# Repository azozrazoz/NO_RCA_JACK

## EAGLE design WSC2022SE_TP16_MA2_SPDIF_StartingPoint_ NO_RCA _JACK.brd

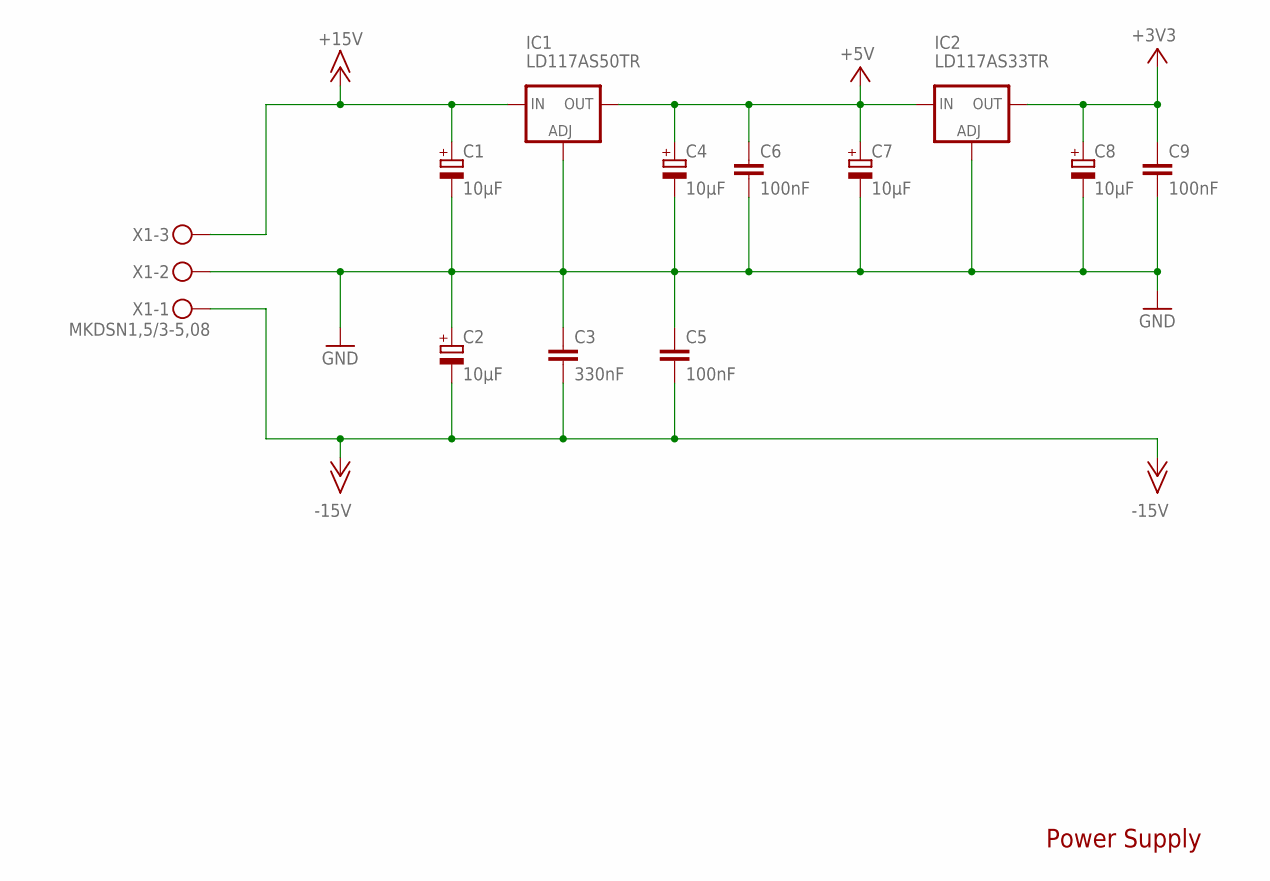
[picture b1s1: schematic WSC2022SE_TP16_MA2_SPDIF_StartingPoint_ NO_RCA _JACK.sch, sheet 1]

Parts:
C1, C2, C4, C7, C8: 10µF; CT3528
C3: 330nF; C0805
C5, C6, C9: 100nF; C0805
IC1: LD117AS50TR; SOT223
IC2: LD117AS33TR; SOT223
X1: MKDSN1,5/3-5,08

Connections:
+3V3: C8.+, C9.1, IC2.2 (OUT), IC2.4 (OUT); also elsewhere on the board
+5V: C4.+, C6.1, C7.+, IC1.2 (OUT), IC1.4 (OUT), IC2.3 (IN); also elsewhere on the board
+15V: C1.+, IC1.3 (IN), X1.3; also elsewhere on the board
-15V: C2.-, C3.2, C5.2, X1.1; also elsewhere on the board
GND: C1.-, C2.+, C3.1, C4.-, C5.1, C6.2, C7.-, C8.-, C9.2, IC1.1 (ADJ), IC2.1 (ADJ), X1.2; also elsewhere on the board

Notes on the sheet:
Power Supply

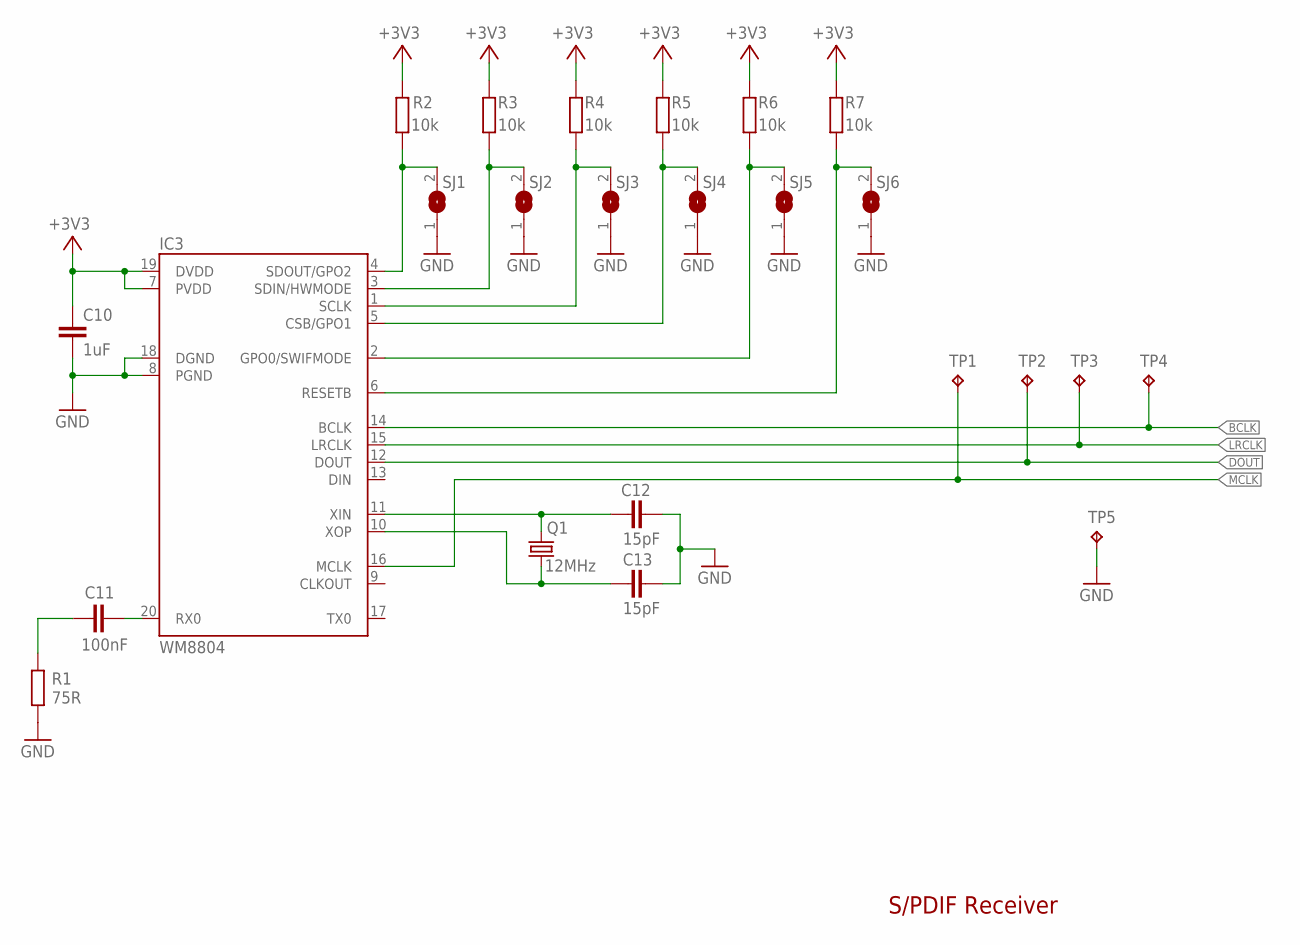
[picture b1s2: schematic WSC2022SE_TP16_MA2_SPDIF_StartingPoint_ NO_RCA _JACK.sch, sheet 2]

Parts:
C10: 1uF; C0805
C11: 100nF; C0805
C12, C13: 15pF; C0805
IC3: WM8804; SSOP20BU
Q1: 12MHz; 5.0X3.2_2
R1: 75R; R0805
R2, R3, R4, R5, R6, R7: 10k; R0805
SJ1, SJ2, SJ3, SJ4, SJ5, SJ6: SJ
TP1, TP2, TP3, TP4, TP5: TPB2,54; B2,54

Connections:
+3V3: C10.1, IC3.7 (PVDD), IC3.19 (DVDD), R2.2, R3.2, R4.2, R5.2, R6.2, R7.2; also elsewhere on the board
BCLK: IC3.14 (BCLK), TP4.TP; also elsewhere on the board
DOUT: IC3.12 (DOUT), TP2.TP; also elsewhere on the board
GND: C10.2, C12.1, C13.1, IC3.8 (PGND), IC3.18 (DGND), R1.1, SJ1.1, SJ2.1, SJ3.1, SJ4.1, SJ5.1, SJ6.1, TP5.TP; also elsewhere on the board
LRCLK: IC3.15 (LRCLK), TP3.TP; also elsewhere on the board
MCLK: IC3.16 (MCLK), TP1.TP; also elsewhere on the board
unnamed: C11.1, R1.2
unnamed: C11.2, IC3.20 (RX0)
unnamed: C13.2, IC3.10 (XOP), Q1.1
unnamed: C12.2, IC3.11 (XIN), Q1.2
unnamed: IC3.4 (SDOUT/GPO2), R2.1, SJ1.2
unnamed: IC3.1 (SCLK), R4.1, SJ3.2
unnamed: IC3.2 (GPO0/SWIFMODE), R6.1, SJ5.2
unnamed: IC3.6 (RESETB), R7.1, SJ6.2
unnamed: IC3.5 (CSB/GPO1), R5.1, SJ4.2
unnamed: IC3.3 (SDIN/HWMODE), R3.1, SJ2.2

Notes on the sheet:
S/PDIF Receiver

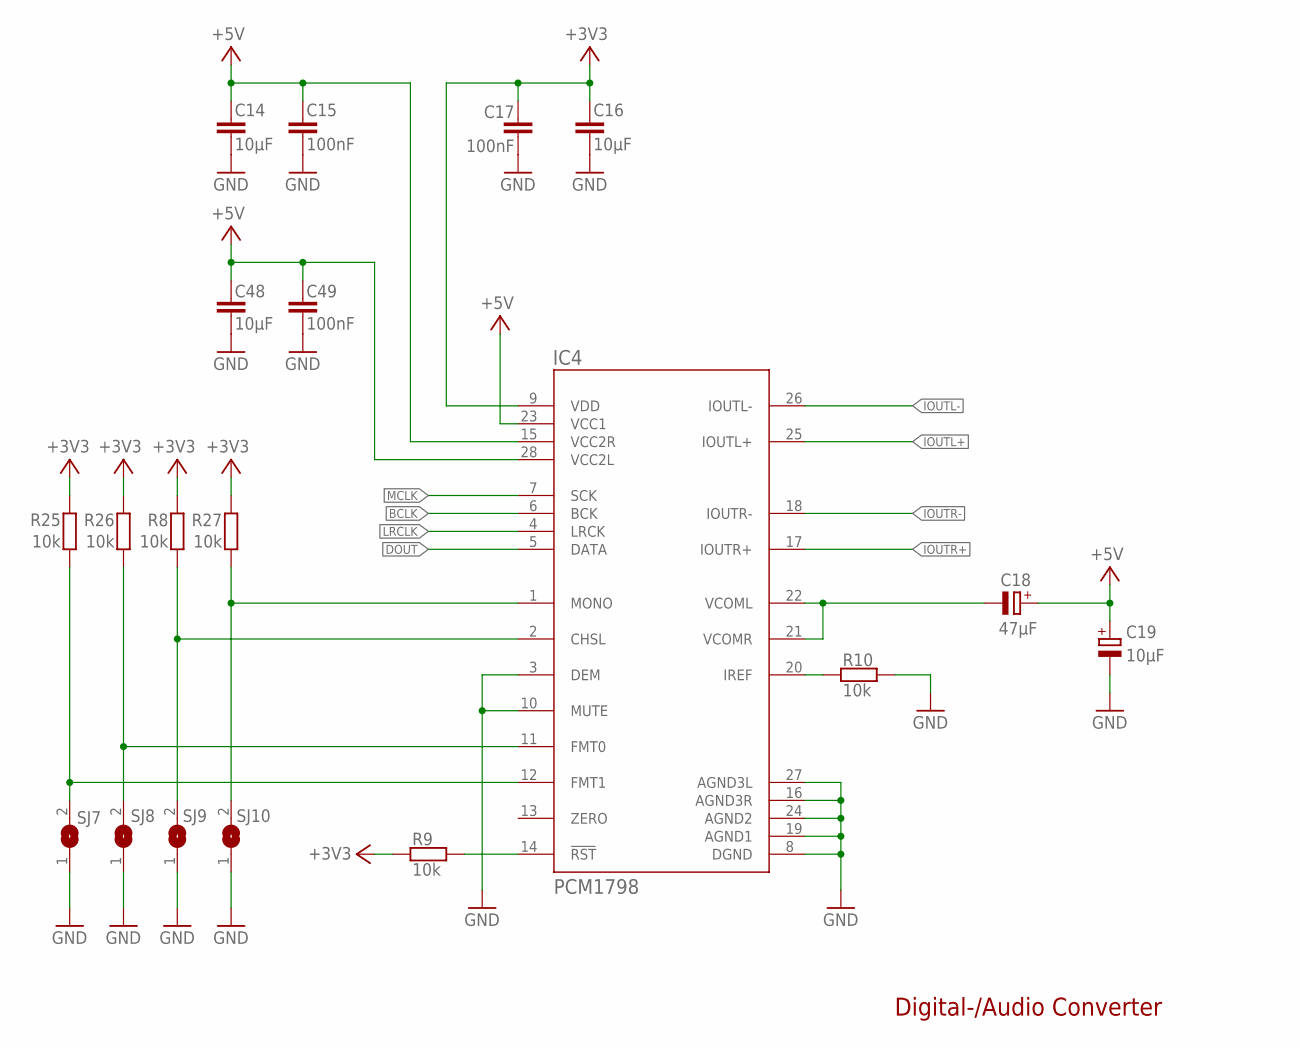
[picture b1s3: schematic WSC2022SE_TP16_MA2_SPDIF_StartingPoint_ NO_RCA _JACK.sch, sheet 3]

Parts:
C14, C16, C48: 10µF; C0805
C15, C17, C49: 100nF; C0805
C18: 47µF; PANASONIC_C
C19: 10µF; PANASONIC_B
IC4: PCM1798; SSOP28
R8, R9, R10, R25, R26, R27: 10k; R0805
SJ7, SJ8, SJ9, SJ10: SJ

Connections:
+3V3: C16.2, C17.2, IC4.9 (VDD), R8.1, R9.1, R25.1, R26.1, R27.1; also elsewhere on the board
+5V: C14.1, C15.1, C18.+, C19.+, C48.1, C49.1, IC4.15 (VCC2R), IC4.23 (VCC1), IC4.28 (VCC2L); also elsewhere on the board
BCLK: IC4.6 (BCK); also elsewhere on the board
DOUT: IC4.5 (DATA); also elsewhere on the board
GND: C14.2, C15.2, C16.1, C17.1, C19.-, C48.2, C49.2, IC4.3 (DEM), IC4.8 (DGND), IC4.10 (MUTE), IC4.16 (AGND3R), IC4.19 (AGND1), IC4.24 (AGND2), IC4.27 (AGND3L), R10.2, SJ7.1, SJ8.1, SJ9.1, SJ10.1; also elsewhere on the board
IOUTL+: IC4.25 (IOUTL+); also elsewhere on the board
IOUTL-: IC4.26 (IOUTL-); also elsewhere on the board
IOUTR+: IC4.17 (IOUTR+); also elsewhere on the board
IOUTR-: IC4.18 (IOUTR-); also elsewhere on the board
LRCLK: IC4.4 (LRCK); also elsewhere on the board
MCLK: IC4.7 (SCK); also elsewhere on the board
unnamed: IC4.1 (MONO), R27.2, SJ10.2
unnamed: IC4.14 (!RST), R9.2
unnamed: IC4.20 (IREF), R10.1
unnamed: C18.-, IC4.21 (VCOMR), IC4.22 (VCOML)
unnamed: IC4.11 (FMT0), R26.2, SJ8.2
unnamed: IC4.12 (FMT1), R25.2, SJ7.2
unnamed: IC4.2 (CHSL), R8.2, SJ9.2

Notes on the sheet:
Digital-/Audio Converter

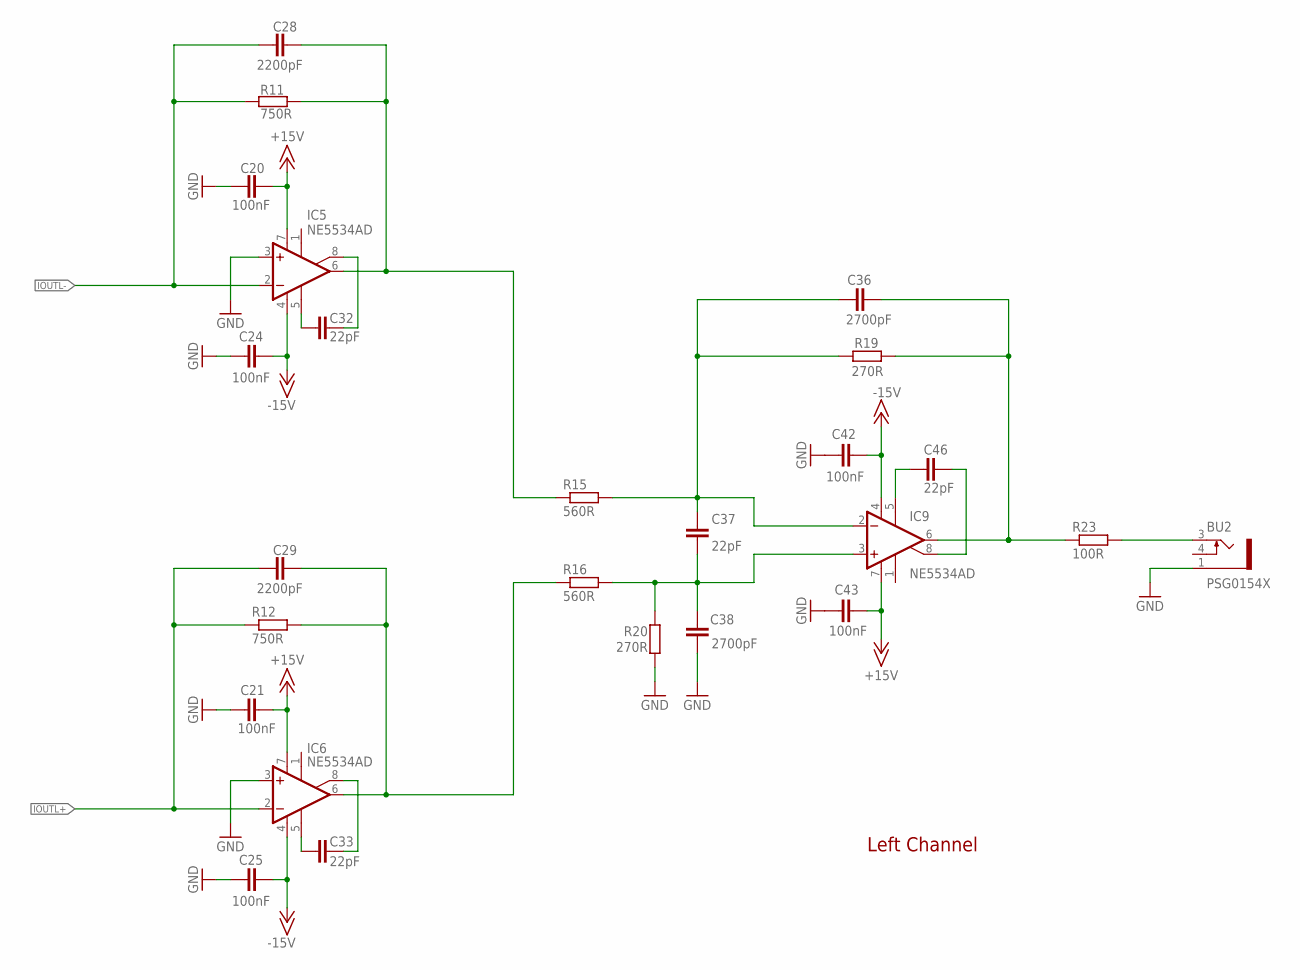
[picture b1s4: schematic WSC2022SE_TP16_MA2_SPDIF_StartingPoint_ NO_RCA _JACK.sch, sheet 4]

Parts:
BU2: PSG0154X; PHONO-3P
C20, C21, C24, C25, C42, C43: 100nF; C0805
C28, C29: 2200pF; C0805
C32, C33, C37, C46: 22pF; C0805
C36, C38: 2700pF; C0805
IC5, IC6, IC9: NE5534AD; SO08
R11, R12: 750R; R0805
R15, R16: 560R; R0805
R19, R20: 270R; R0805
R23: 100R; R0805

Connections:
+15V: C20.1, C21.1, C43.1, IC5.7 (V+), IC6.7 (V+), IC9.7 (V+); also elsewhere on the board
-15V: C24.1, C25.1, C42.1, IC5.4 (V-), IC6.4 (V-), IC9.4 (V-); also elsewhere on the board
GND: BU2.1, C20.2, C21.2, C24.2, C25.2, C38.2, C42.2, C43.2, IC5.3 (+IN), IC6.3 (+IN), R20.1; also elsewhere on the board
IOUTL+: C29.1, IC6.2 (-IN), R12.1; also elsewhere on the board
IOUTL-: C28.1, IC5.2 (-IN), R11.1; also elsewhere on the board
unnamed: C33.1, IC6.8 (ON/CMP)
unnamed: C33.2, IC6.5 (CMP)
unnamed: C37.2, C38.1, IC9.3 (+IN), R16.2, R20.2
unnamed: C32.2, IC5.5 (CMP)
unnamed: C32.1, IC5.8 (ON/CMP)
unnamed: C36.2, C37.1, IC9.2 (-IN), R15.2, R19.1
unnamed: C36.1, IC9.6 (OUT), R19.2, R23.1
unnamed: C46.1, IC9.5 (CMP)
unnamed: C46.2, IC9.8 (ON/CMP)
OUT-CHANNEL-L: BU2.3, R23.2
VOUTL+: C29.2, IC6.6 (OUT), R12.2, R16.1
VOUTL-: C28.2, IC5.6 (OUT), R11.2, R15.1

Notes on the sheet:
Left Channel

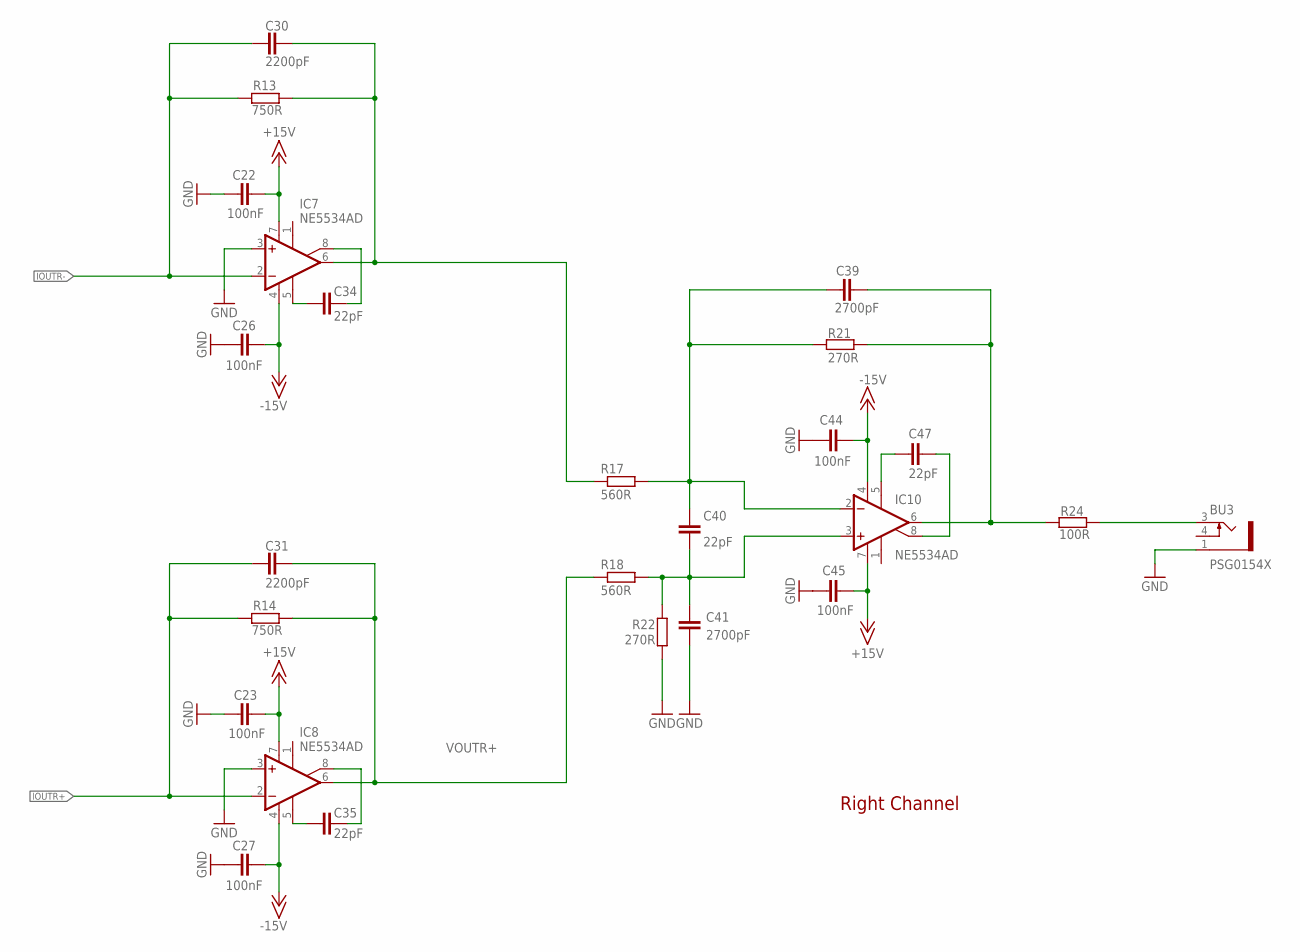
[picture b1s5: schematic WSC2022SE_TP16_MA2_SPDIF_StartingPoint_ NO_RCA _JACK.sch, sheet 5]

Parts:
BU3: PSG0154X; PHONO-3P
C22, C23, C26, C27, C44, C45: 100nF; C0805
C30, C31: 2200pF; C0805
C34, C35, C40, C47: 22pF; C0805
C39, C41: 2700pF; C0805
IC7, IC8, IC10: NE5534AD; SO08
R13, R14: 750R; R0805
R17, R18: 560R; R0805
R21, R22: 270R; R0805
R24: 100R; R0805

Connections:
+15V: C22.1, C23.1, C45.1, IC7.7 (V+), IC8.7 (V+), IC10.7 (V+); also elsewhere on the board
-15V: C26.1, C27.1, C44.1, IC7.4 (V-), IC8.4 (V-), IC10.4 (V-); also elsewhere on the board
GND: BU3.1, C22.2, C23.2, C26.2, C27.2, C41.2, C44.2, C45.2, IC7.3 (+IN), IC8.3 (+IN), R22.1; also elsewhere on the board
IOUTR+: C31.1, IC8.2 (-IN), R14.1; also elsewhere on the board
IOUTR-: C30.1, IC7.2 (-IN), R13.1; also elsewhere on the board
unnamed: C34.1, IC7.8 (ON/CMP)
unnamed: C39.2, C40.1, IC10.2 (-IN), R17.2, R21.1
unnamed: C39.1, IC10.6 (OUT), R21.2, R24.1
unnamed: C47.1, IC10.5 (CMP)
unnamed: C47.2, IC10.8 (ON/CMP)
unnamed: C34.2, IC7.5 (CMP)
unnamed: C40.2, C41.1, IC10.3 (+IN), R18.2, R22.2
unnamed: C35.1, IC8.8 (ON/CMP)
unnamed: C35.2, IC8.5 (CMP)
OUT-CHANNEL-R: BU3.3, R24.2
VOUTR+: C31.2, IC8.6 (OUT), R14.2, R18.1
VOUTR-: C30.2, IC7.6 (OUT), R13.2, R17.1

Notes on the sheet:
Right Channel

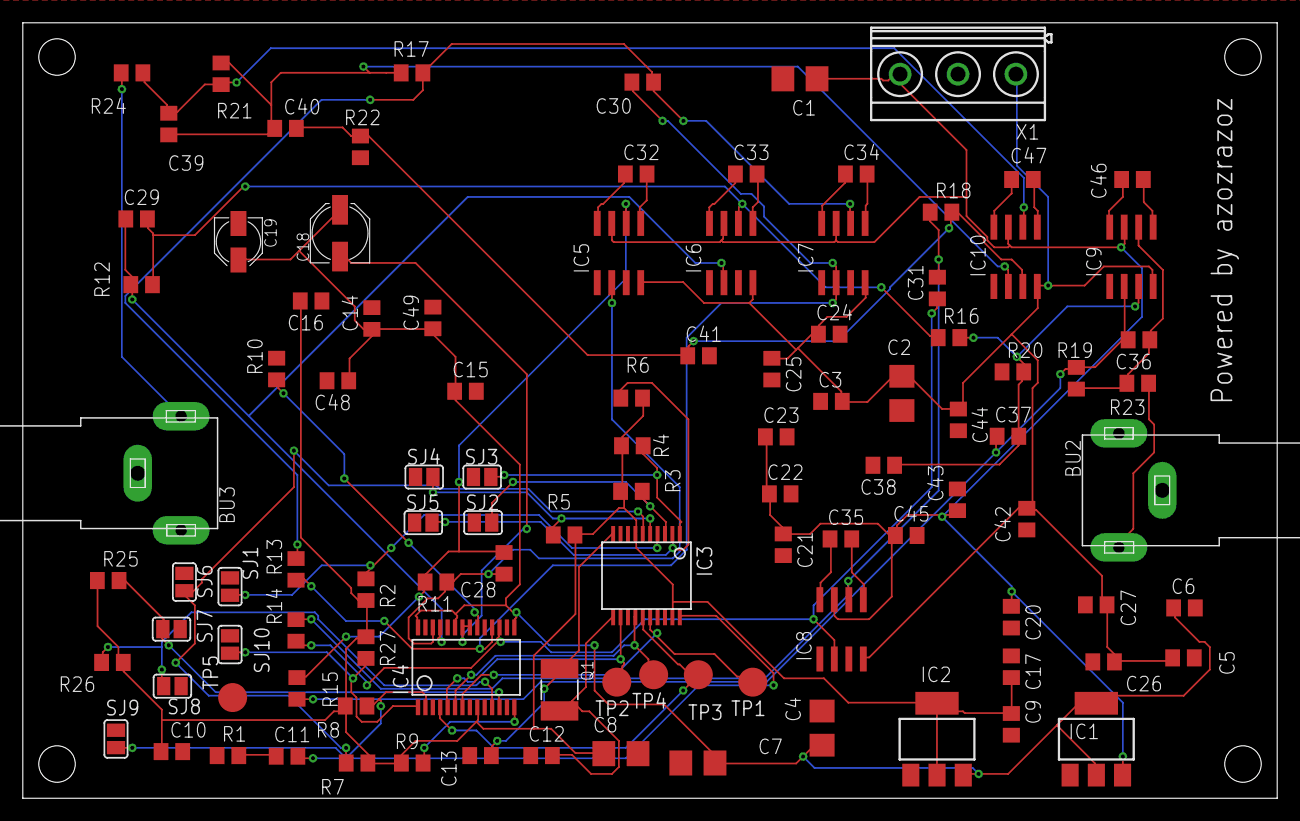
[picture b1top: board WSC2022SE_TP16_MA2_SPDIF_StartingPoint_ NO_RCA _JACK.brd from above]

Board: 2 copper layers, 110.0 x 68.0 mm, 105 parts (0 on the bottom side), 54 nets.

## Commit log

2023-02-06 add board and scheme

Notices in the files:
parts and their libraries:
crystal-geyer_V1_0: Copyright: Geyer-Electronic
